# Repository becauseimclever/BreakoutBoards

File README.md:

# BreakoutBoards
Collection of various SMT breakout boards

## ADS112C04IPWR
Texas Instruments 16-bit 4 channel ADC using the I²C bus.

https://www.ti.com/store/ti/en/p/product/?p=ADS112C04IPWR

## DRV2605LDGSR
Texas Instruments motor driver for haptic feedback. 2V~5.5V I²C

https://www.ti.com/store/ti/en/p/product/?p=DRV2605LDGSR

## PCM1780DBQR
Texas Instruments 24-bit 2 channel DAC using the I²S bus.

https://www.ti.com/store/ti/en/p/product/?p=PCM1780DBQR

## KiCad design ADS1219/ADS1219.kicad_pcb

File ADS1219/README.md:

# ADS1219 Analog to Digital Breakout board

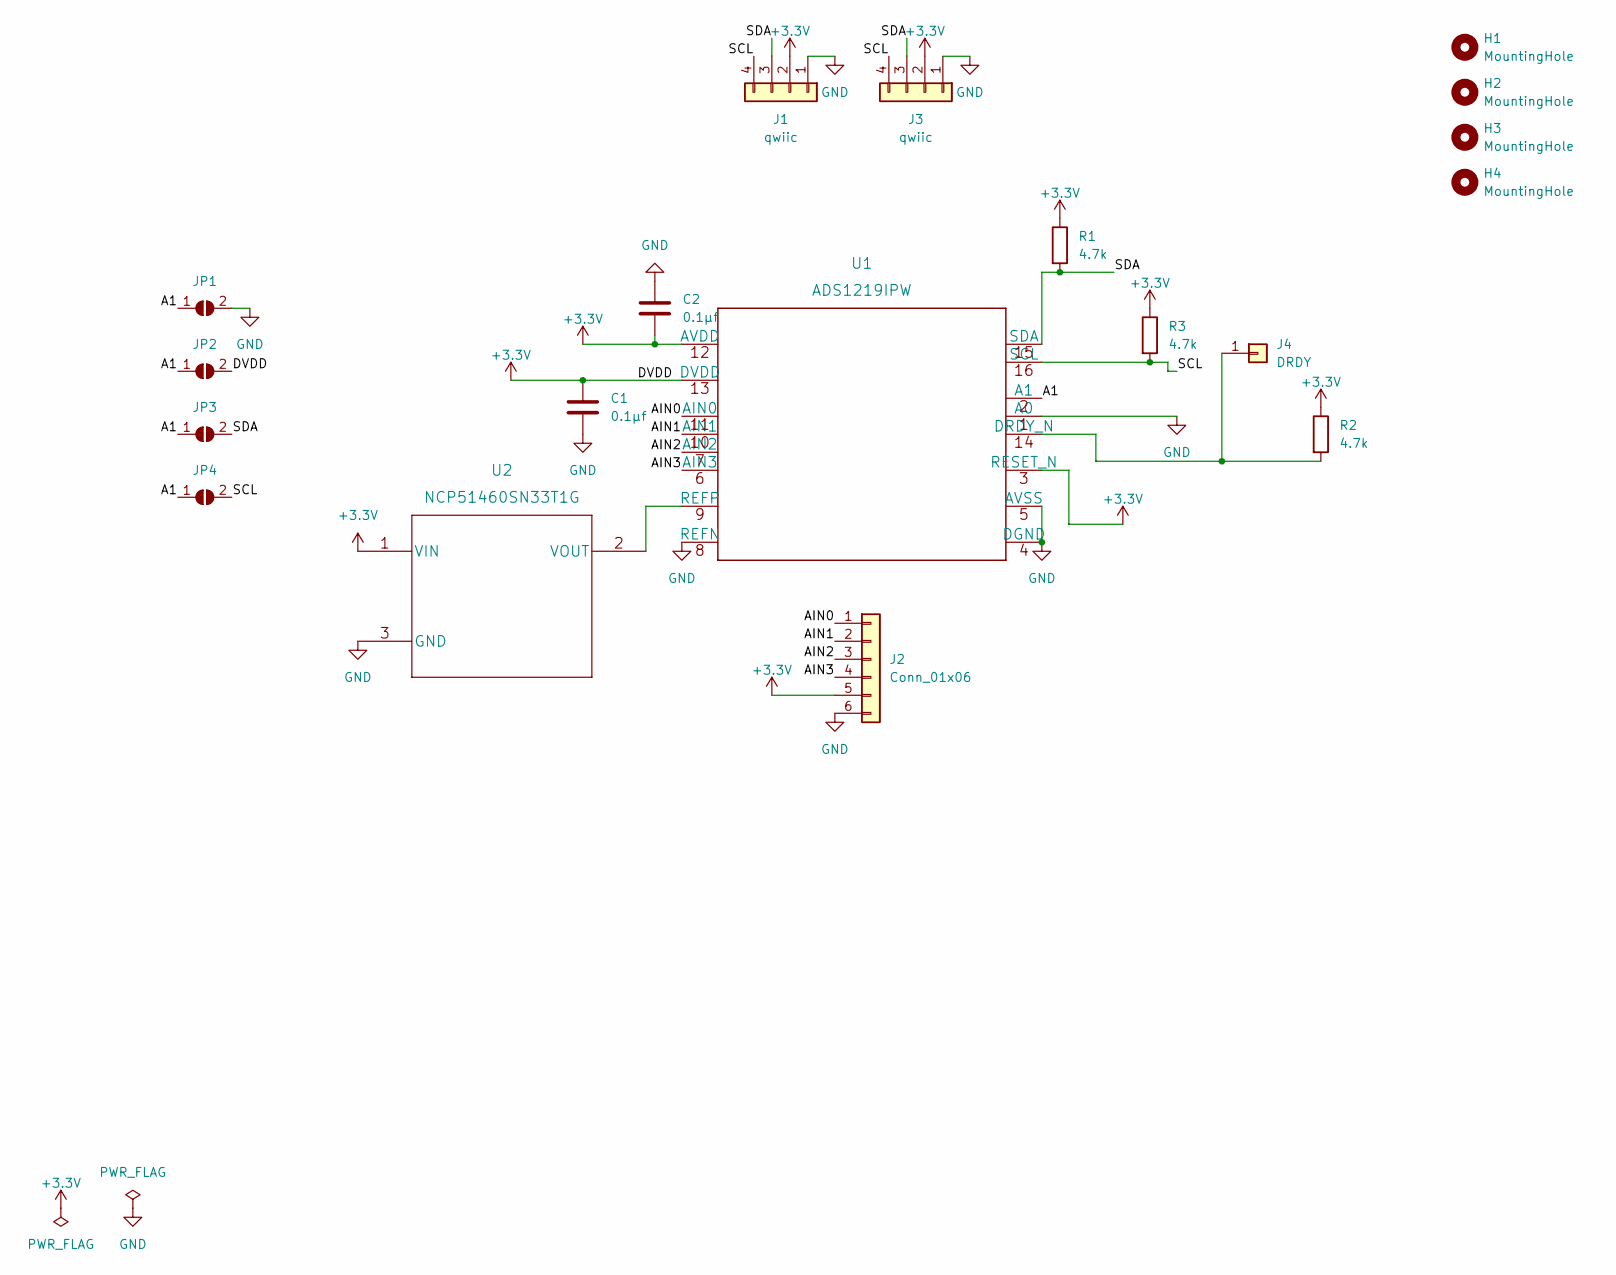
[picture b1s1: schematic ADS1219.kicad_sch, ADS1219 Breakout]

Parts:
C1, C2: 0.1μf; C_0805_2012Metric_Pad1.18x1.45mm_HandSolder
H1, H2, H3, H4: MountingHole; MountingHole_2.5mm
J1, J3: qwiic; JST_SH_SM04B-SRSS-TB_1x04-1MP_P1.00mm_Horizontal
J2: Conn_01x06; PinHeader_1x06_P2.54mm_Vertical
J4: DRDY; PinHeader_1x01_P2.54mm_Vertical
JP1, JP2, JP3, JP4: SolderJumper_2_Open; SolderJumper-2_P1.3mm_Open_TrianglePad1.0x1.5mm
R1, R2, R3: 4.7k; R_0805_2012Metric_Pad1.20x1.40mm_HandSolder
U1: ADS1219IPW
U2: NCP51460SN33T1G

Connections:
+3.3V: C1.2, C2.1, J1.2, J2.5, J3.2, JP2.2 (B), R1.1, R2.1, R3.1, U1.3 (RESET_N), U1.12 (AVDD), U1.13 (DVDD), U2.1 (VIN); also elsewhere on the board
/A1: JP1.1 (A), JP2.1 (A), JP3.1 (A), JP4.1 (A), U1.2 (A1)
/AIN0: J2.1, U1.11 (AIN0)
/AIN1: J2.2, U1.10 (AIN1)
/AIN2: J2.3, U1.7 (AIN2)
/AIN3: J2.4, U1.6 (AIN3)
/SCL: J1.4, J3.4, JP4.2 (B), R3.2, U1.16 (SCL)
/SDA: J1.3, J3.3, JP3.2 (B), R1.2, U1.15 (SDA)
GND: C1.1, C2.2, J1.1, J2.6, J3.1, JP1.2 (B), U1.1 (A0), U1.4 (DGND), U1.5 (AVSS), U1.8 (REFN), U2.3 (GND); also elsewhere on the board
unnamed: J4.1, R2.2, U1.14 (DRDY_N)
unnamed: U1.9 (REFP), U2.2 (VOUT)

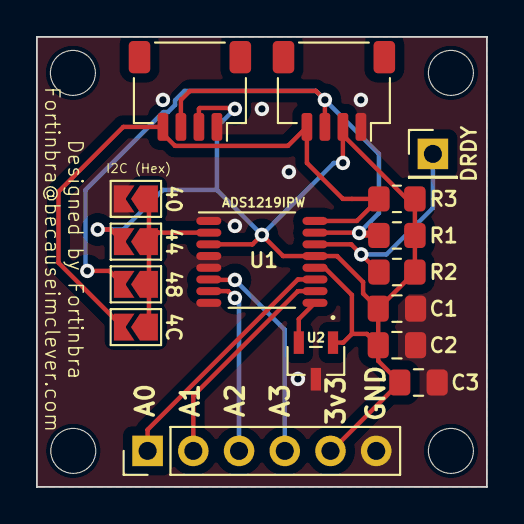
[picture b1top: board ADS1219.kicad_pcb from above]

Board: 2 copper layers, 25.0 x 25.0 mm, 20 parts (0 on the bottom side), 11 nets.

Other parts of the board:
C3: 0.1μF; C_0805_2012Metric_Pad1.18x1.45mm_HandSolder

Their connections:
+3.3V: C3.1; also elsewhere on the board
GND: C3.2; also elsewhere on the board

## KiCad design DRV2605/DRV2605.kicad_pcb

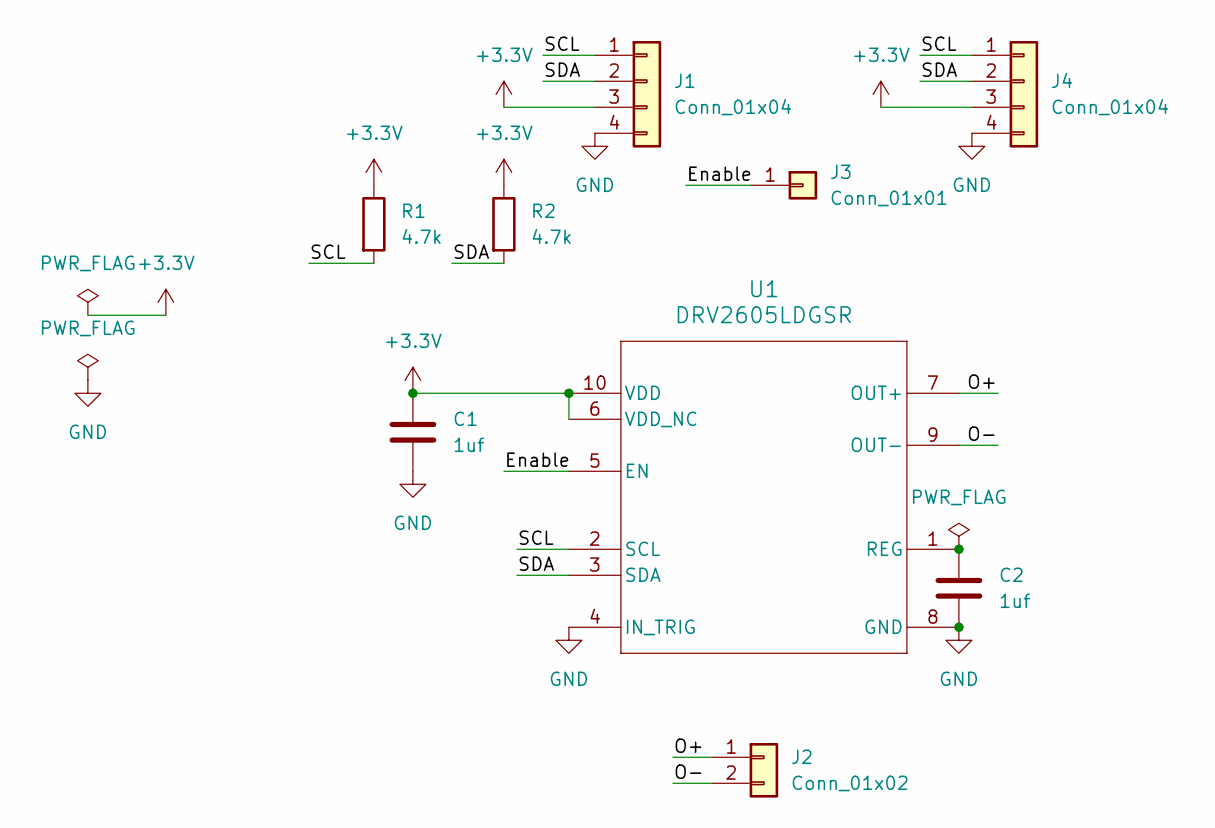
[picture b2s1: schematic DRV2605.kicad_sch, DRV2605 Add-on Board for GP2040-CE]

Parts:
C1, C2: 1uf; C_0603_1608Metric_Pad1.08x0.95mm_HandSolder
J1, J4: Conn_01x04; JST_SH_SM04B-SRSS-TB_1x04-1MP_P1.00mm_Horizontal
J2: Conn_01x02; JST_SH_SM02B-SRSS-TB_1x02-1MP_P1.00mm_Horizontal
J3: Conn_01x01; PinHeader_1x01_P2.54mm_Vertical
R1, R2: 4.7k; R_0603_1608Metric_Pad0.98x0.95mm_HandSolder
U1: DRV2605LDGSR; DGS0010A

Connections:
+3.3V: C1.1, J1.3, J4.3, R1.1, R2.1, U1.6 (VDD_NC), U1.10 (VDD)
/Enable: J3.1, U1.5 (EN)
/O+: J2.1, U1.7 (OUT+)
/O-: J2.2, U1.9 (OUT-)
/SCL: J1.1, J4.1, R1.2, U1.2 (SCL)
/SDA: J1.2, J4.2, R2.2, U1.3 (SDA)
GND: C1.2, C2.2, J1.4, J4.4, U1.4 (IN_TRIG), U1.8 (GND)
unnamed: C2.1, U1.1 (REG)

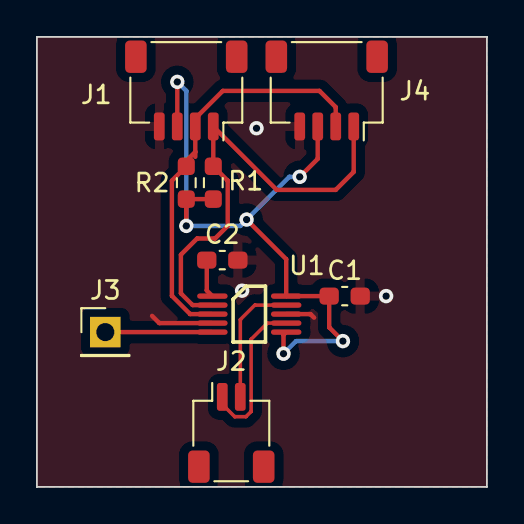
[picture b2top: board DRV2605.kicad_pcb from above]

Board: 2 copper layers, 25.0 x 25.0 mm, 9 parts (0 on the bottom side), 8 nets.

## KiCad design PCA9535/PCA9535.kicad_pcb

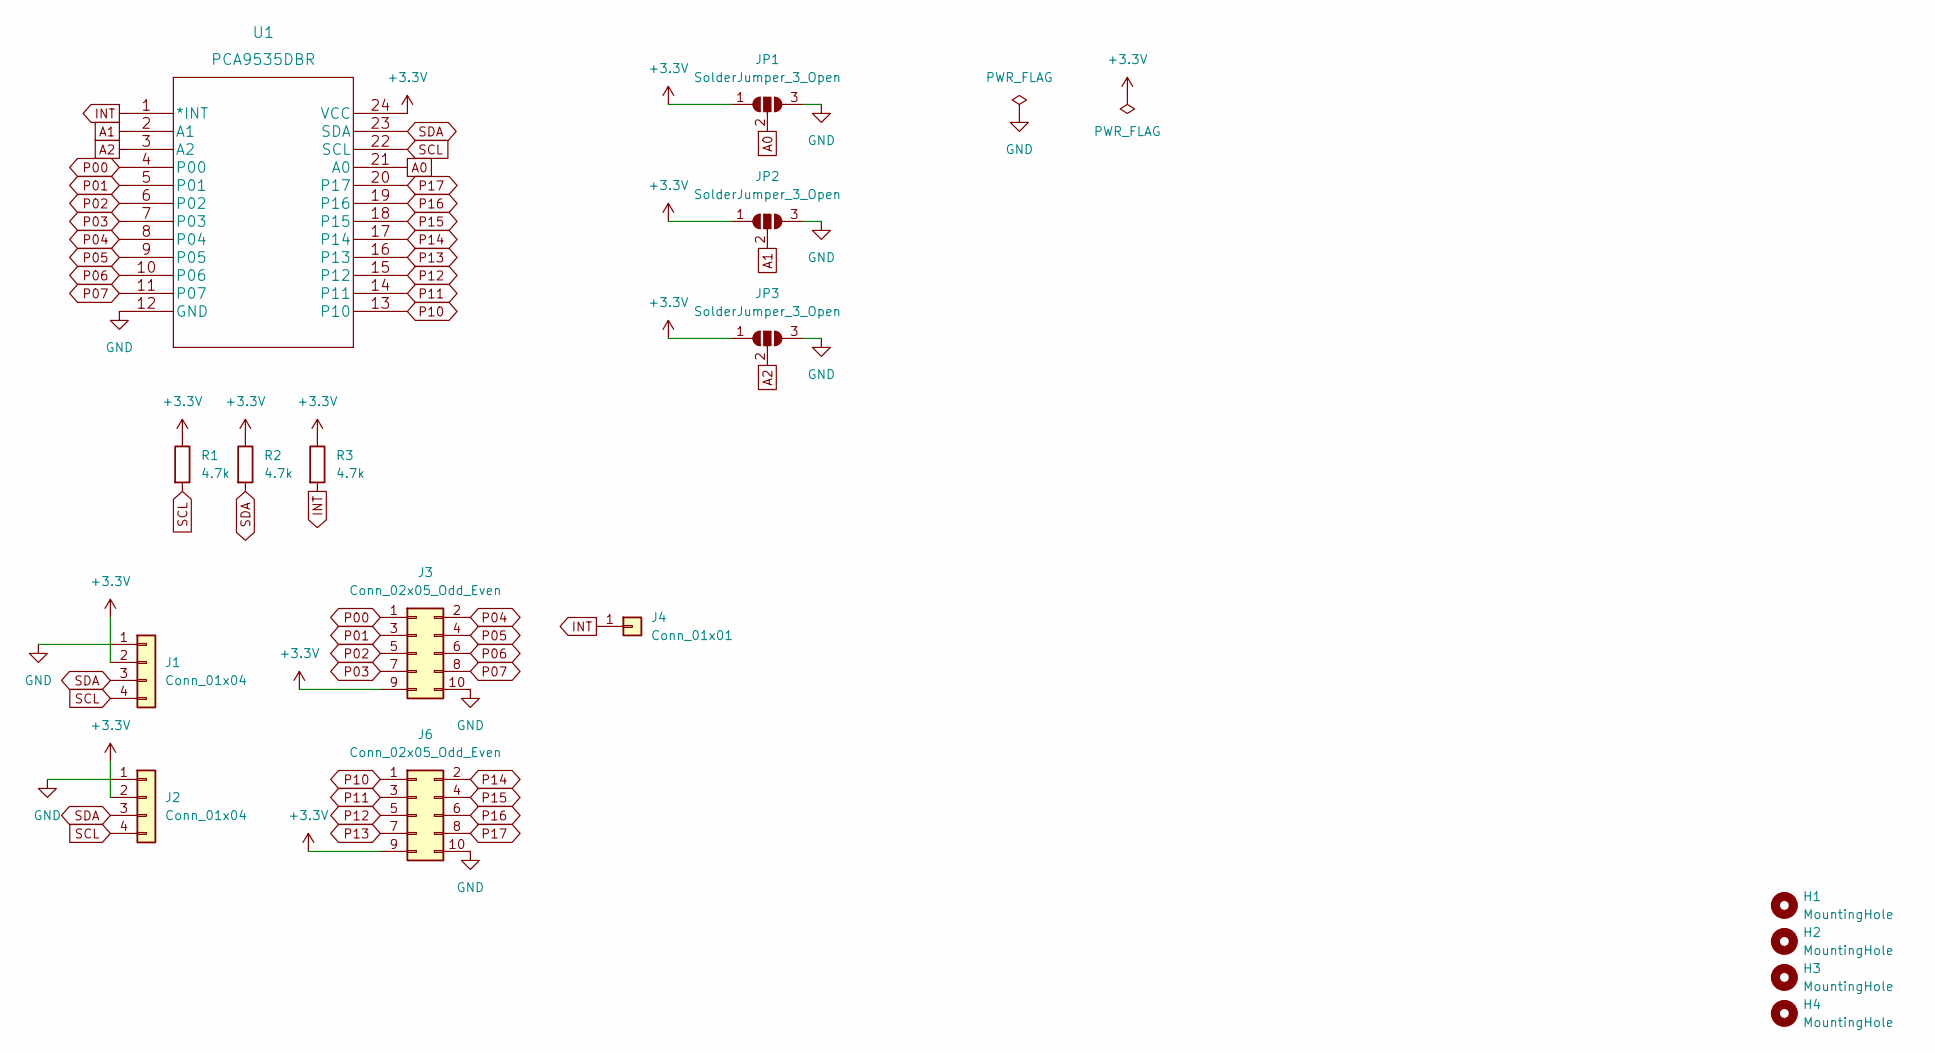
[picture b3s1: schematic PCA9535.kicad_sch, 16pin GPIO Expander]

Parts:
H1, H2, H3, H4: MountingHole; MountingHole_2.5mm
J1, J2: Conn_01x04; JST_SH_SM04B-SRSS-TB_1x04-1MP_P1.00mm_Horizontal
J3, J6: Conn_02x05_Odd_Even; PinHeader_2x05_P2.54mm_Vertical
J4: Conn_01x01; PinHeader_1x01_P2.54mm_Vertical
JP1, JP2, JP3: SolderJumper_3_Open; SolderJumper-3_P1.3mm_Open_Pad1.0x1.5mm
R1, R2, R3: 4.7k; R_0805_2012Metric_Pad1.20x1.40mm_HandSolder
U1: PCA9535DBR

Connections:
+3.3V: J1.2, J2.2, J3.9, J6.9, JP1.1 (A), JP2.1 (A), JP3.1 (A), R1.1, R2.1, R3.1, U1.24 (VCC)
A0: JP1.2 (C), U1.21 (A0)
A1: JP2.2 (C), U1.2 (A1)
A2: JP3.2 (C), U1.3 (A2)
GND: J1.1, J2.1, J3.10, J6.10, JP1.3 (B), JP2.3 (B), JP3.3 (B), U1.12 (GND)
INT: J4.1, R3.2, U1.1 (*INT)
P00: J3.1, U1.4 (P00)
P01: J3.3, U1.5 (P01)
P02: J3.5, U1.6 (P02)
P03: J3.7, U1.7 (P03)
P04: J3.2, U1.8 (P04)
P05: J3.4, U1.9 (P05)
P06: J3.6, U1.10 (P06)
P07: J3.8, U1.11 (P07)
P10: J6.1, U1.13 (P10)
P11: J6.3, U1.14 (P11)
P12: J6.5, U1.15 (P12)
P13: J6.7, U1.16 (P13)
P14: J6.2, U1.17 (P14)
P15: J6.4, U1.18 (P15)
P16: J6.6, U1.19 (P16)
P17: J6.8, U1.20 (P17)
SCL: J1.4, J2.4, R1.2, U1.22 (SCL)
SDA: J1.3, J2.3, R2.2, U1.23 (SDA)

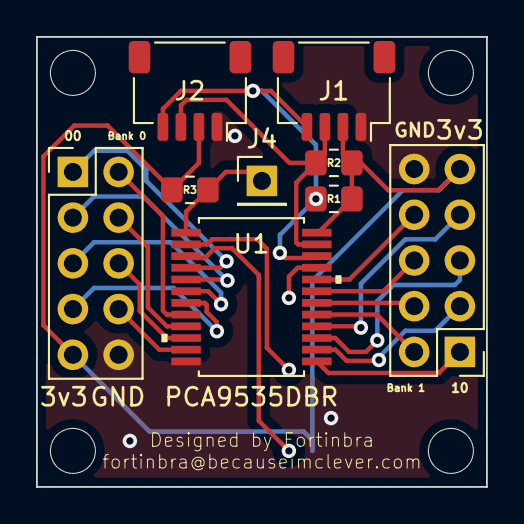
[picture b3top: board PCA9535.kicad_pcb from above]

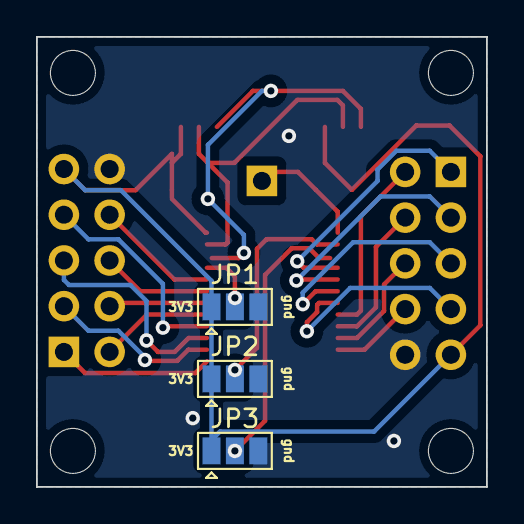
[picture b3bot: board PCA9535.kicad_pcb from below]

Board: 2 copper layers, 25.0 x 25.0 mm, 16 parts (3 on the bottom side), 24 nets.

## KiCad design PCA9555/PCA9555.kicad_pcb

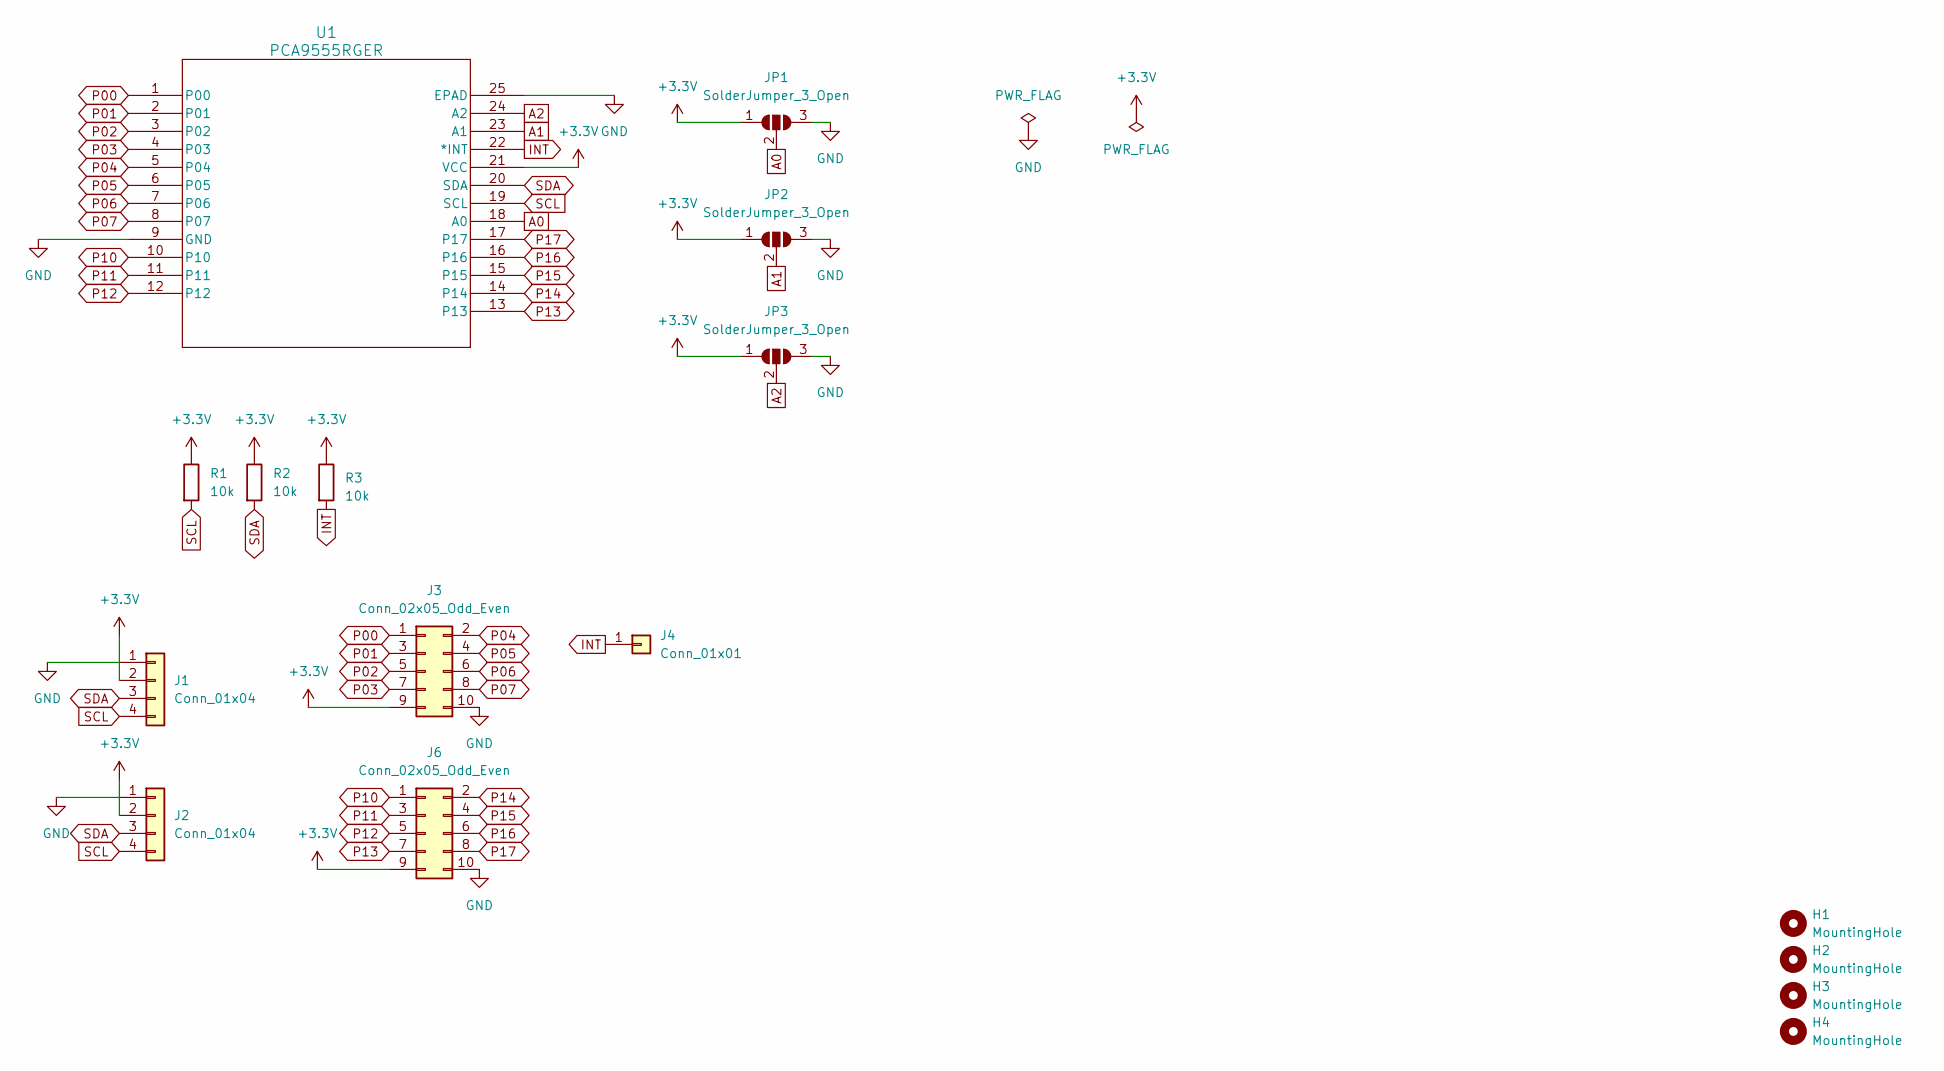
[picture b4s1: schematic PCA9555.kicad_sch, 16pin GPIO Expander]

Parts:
H1, H2, H3, H4: MountingHole; MountingHole_2.5mm
J1, J2: Conn_01x04; JST_SH_SM04B-SRSS-TB_1x04-1MP_P1.00mm_Horizontal
J3, J6: Conn_02x05_Odd_Even; PinHeader_2x05_P2.54mm_Vertical
J4: Conn_01x01; PinHeader_1x01_P2.54mm_Vertical
JP1, JP2, JP3: SolderJumper_3_Open; SolderJumper-3_P1.3mm_Open_Pad1.0x1.5mm
R1, R2, R3: 10k; R_0805_2012Metric_Pad1.20x1.40mm_HandSolder
U1: PCA9555RGER; RGE24_2P1X2P1

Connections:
+3.3V: J1.2, J2.2, J3.9, J6.9, JP1.1 (A), JP2.1 (A), JP3.1 (A), R1.1, R2.1, R3.1, U1.21 (VCC)
A0: JP1.2 (C), U1.18 (A0)
A1: JP2.2 (C), U1.23 (A1)
A2: JP3.2 (C), U1.24 (A2)
GND: J1.1, J2.1, J3.10, J6.10, JP1.3 (B), JP2.3 (B), JP3.3 (B), U1.9 (GND), U1.25 (EPAD)
INT: J4.1, R3.2, U1.22 (*INT)
P00: J3.1, U1.1 (P00)
P01: J3.3, U1.2 (P01)
P02: J3.5, U1.3 (P02)
P03: J3.7, U1.4 (P03)
P04: J3.2, U1.5 (P04)
P05: J3.4, U1.6 (P05)
P06: J3.6, U1.7 (P06)
P07: J3.8, U1.8 (P07)
P10: J6.1, U1.10
P11: J6.3, U1.11
P12: J6.5, U1.12
P13: J6.7, U1.13
P14: J6.2, U1.14
P15: J6.4, U1.15
P16: J6.6, U1.16
P17: J6.8, U1.17
SCL: J1.4, J2.4, R1.2, U1.19 (SCL)
SDA: J1.3, J2.3, R2.2, U1.20 (SDA)

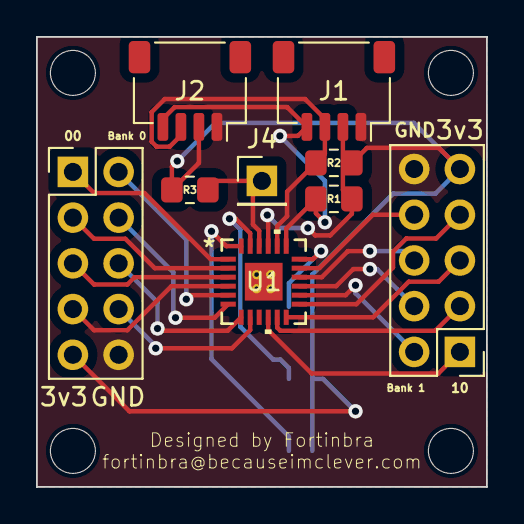
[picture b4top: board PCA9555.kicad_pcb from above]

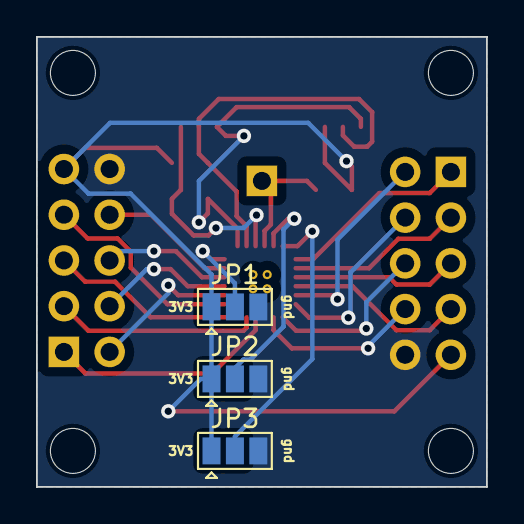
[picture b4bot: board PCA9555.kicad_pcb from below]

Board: 2 copper layers, 25.0 x 25.0 mm, 16 parts (3 on the bottom side), 24 nets.

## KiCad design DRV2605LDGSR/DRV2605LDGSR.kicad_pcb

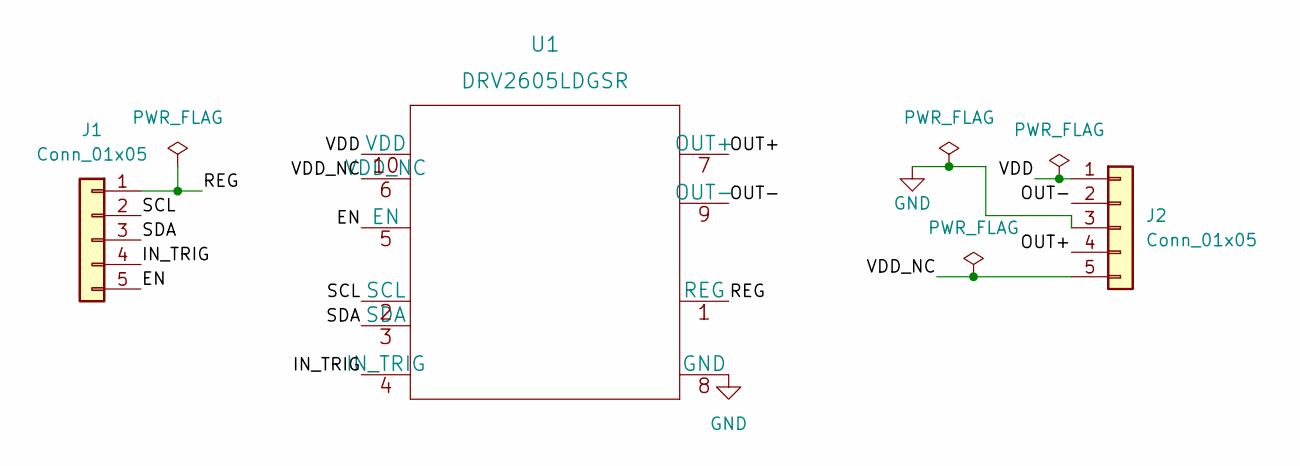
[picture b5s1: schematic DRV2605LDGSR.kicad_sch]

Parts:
J1, J2: Conn_01x05; PinHeader_1x05_P2.54mm_Vertical
U1: DRV2605LDGSR

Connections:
/EN: J1.5, U1.5 (EN)
/IN_TRIG: J1.4, U1.4 (IN_TRIG)
/OUT+: J2.4, U1.7 (OUT+)
/OUT-: J2.2, U1.9 (OUT-)
/REG: J1.1, U1.1 (REG)
/SCL: J1.2, U1.2 (SCL)
/SDA: J1.3, U1.3 (SDA)
/VDD: J2.1, U1.10 (VDD)
/VDD_NC: J2.5, U1.6 (VDD_NC)
GND: J2.3, U1.8 (GND)

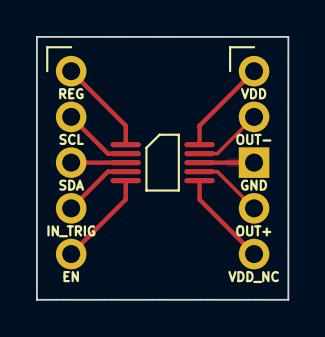
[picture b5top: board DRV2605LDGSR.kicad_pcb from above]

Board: 2 copper layers, 14.0 x 14.6 mm, 3 parts (0 on the bottom side), 10 nets.

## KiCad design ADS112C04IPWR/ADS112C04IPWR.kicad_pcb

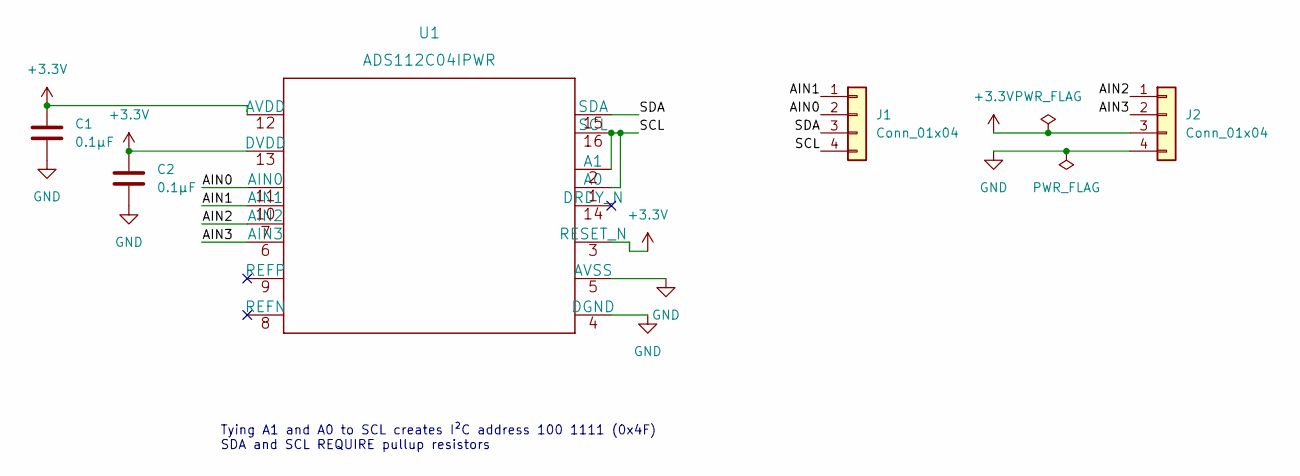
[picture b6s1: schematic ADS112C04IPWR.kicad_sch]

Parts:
C1, C2: 0.1μF; C_0201_0603Metric_Pad0.64x0.40mm_HandSolder
J1, J2: Conn_01x04; PinHeader_1x04_P2.54mm_Vertical
U1: ADS112C04IPWR

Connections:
+3V3: C1.1, C2.1, J2.3, U1.3 (RESET_N), U1.12 (AVDD), U1.13 (DVDD)
/AIN0: J1.2, U1.11 (AIN0)
/AIN1: J1.1, U1.10 (AIN1)
/AIN2: J2.1, U1.7 (AIN2)
/AIN3: J2.2, U1.6 (AIN3)
/SCL: J1.4, U1.1 (A0), U1.2 (A1), U1.16 (SCL)
/SDA: J1.3, U1.15 (SDA)
GND: C1.2, C2.2, J2.4, U1.4 (DGND), U1.5 (AVSS)

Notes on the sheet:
Tying A1 and A0 to SCL creates I²C address 100 1111 (0x4F) SDA and SCL REQUIRE pullup resistors

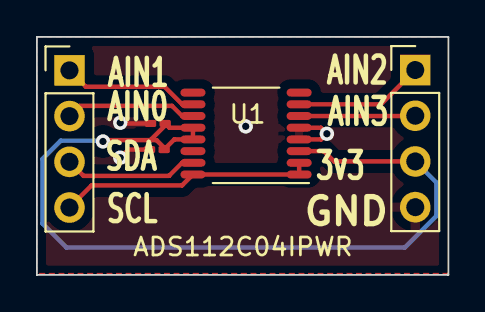
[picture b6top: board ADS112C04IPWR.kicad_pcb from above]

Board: 2 copper layers, 22.9 x 13.2 mm, 5 parts (0 on the bottom side), 8 nets.

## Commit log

2022-02-26 Adding first breakout board
2022-02-26 Adding PCM1780DBQR
2022-02-26 ADS112C04IPWR
2022-02-28 Updating Readme file
2022-02-28 Adding thumbstick
2022-03-25 Updating the ADC
2022-03-25 Syncing
2022-03-27 Sync
2022-04-04 Revision One
2022-04-04 Starting work on Thumbstick (THB001P)
2022-04-14 Generating gerbers for board
2022-05-10 New breakout started, ADS1219, because th ADS112C04 is out of stock everywhere
2022-07-17 futher revisions
2022-08-08 ADC nearly complete
2022-08-16 Adding new board
2022-08-17 Adding some meat to the schematic
2022-08-24 progress
2022-08-27 Updating GPIO expansion board
2022-08-31 Figured out solder jumpers, kinda
2022-09-20 Adding slider for address programming
2022-09-24 Revert "Adding slider for address programming"
    This reverts commit 487b6004aa2a68d069b1c4fba08261144dd1fb57.
2022-09-24 Revert "Revert "Adding slider for address programming""
    This reverts commit 9266481bdb07586092e7bd52b8f18c584fadba43.
2022-09-24 syncing again...
2022-09-24 Futher Progress on the gpio
2022-09-25 Finalizing the 16pin expander
2022-10-15 Syncing backups
2022-10-20 Updating the adc board with a vref
2023-02-05 Adding vref and drdy
2023-02-19 Updating to KiCad 7
2023-05-22 PCA9555
2023-06-11 Cleaning up repo
2023-08-11 Starting Cleanup
2023-08-11 Continuing cleanup
2023-08-11 More files removed
2023-08-11 Cleaning up ADS1219 board folders
2023-08-11 new images
2023-08-11 Adding spec sheet
2023-10-07 add C3, 0.1uF decoupling cap for voltage reference IC - also rework board text labels

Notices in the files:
parts and their libraries:
Copyright 2021 Accelerated Designs. All rights reserved.
